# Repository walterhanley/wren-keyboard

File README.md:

# Wren Keyboard

## Table of Contents
- [Introduction](https://github.com/walterhanley/wren-keyboard#introduction)
- [Controller](https://github.com/walterhanley/wren-keyboard#controller)
- [PCB](https://github.com/walterhanley/wren-keyboard#pcb)
- [Case and Plate](https://github.com/walterhanley/wren-keyboard#case-and-plate)
- [Software](https://github.com/walterhanley/wren-keyboard#software)
- [Cost Estimates and Purchasing](https://github.com/walterhanley/wren-keyboard#cost-estimates-and-purchasing)
- [BOM](https://github.com/walterhanley/wren-keyboard#bom)
- [Build Guide](https://github.com/walterhanley/wren-keyboard#build-guide)

## Introduction
The Wren is a split ergonomic "system keyboard". It takes heavy inspiration from the Lily58, [Afternoon Labs' Breeze](https://afternoonlabs.com/breeze/), and [SplitKB's Kyria](https://blog.splitkb.com/blog/introducing-the-kyria), in addition to employing a case similar to the Corne's.

My primary keyboard for the last few years has been Prime Keyboards' prime_o, before which I used a handwired Planck. On both I made pretty heavy use of the numpad. I grew to appreciate the prime\_o's physical one, though, mostly because I spend a lot of time in Excel at my day job and like using the mouse and numpad simultaneously. I've been wanting to switch to ergo for a while, but I was annoyed by the thought of having to use a separate numpad to recreate that experience. This project was an attempt to solve that problem.

My original design simply incorporated a southpaw numpad. After some feedback, though, I decided to reinvent it as a "system keyboard" modeled after the old system cameras. The repository includes a universal PCB (incorporating break-away tabs) and plates to make four boards, each reversible:
- A Lilly58/Kyria-inspired split board, with no extra keys;
- An extended layout with a 4x4 numpad;
- An extended layout with a traditional nav cluster; and
- A small 4x4 macropad (nicknamed Egg).

Each of these boards (besides the macropad) can be combined with the others in a split setup, so users can take their pick of a right or left nav cluster/numpad, or combine both in the same board. You could even just use two of the basic boards together for a more traditional layout, though I'm sure there are more elegant designs out there for that.

## Controller
The Wren uses a Pro Micro-compatible footprint, but is designed around the Elite-C's extra I/O pins on the numpad board. With just a Pro Micro, the outer column won't work. I _think_ you could get a Nice!Nano to full compatibility with some creative soldering from the mid-board I/O pins to the appropriate pins on the Elite-C footprint, but I haven't spent any time on this myself.

## PCB
The PCB uses reversible, MX-compatible footprints. There isn't hot-swap support yet, in large part because I didn't want to deal with the structural considerations of those sockets. If someone else wanted to make a pull request for a hotswap version, though, I'd be happy to merge it in.

The PCB is also specifically designed around rotary encoders with a diameter less than 0.5". I'm using Kilo 50 sized knobs, but others in a similar size class will work well, too.

## Case and Plate
This repository includes a top and bottom plate designed around M2 screws and standoffs. The bottom plate can be manufactured out of FR4 PCB material by any manufacturer; this will likely be the most cost-effective option. The top plate cannot be manufactured by my preferred PCB fabricator, JLCPCB, but your milage may vary. Instead, I used the .eps files included in the [Case folder](https://github.com/walterhanley/wren-keyboard/tree/main/Case) to have my top plates manufactured in stainless steel by SendCutSend. In my experience these plates are an extremely tight fit around Kailh Box switches, but considering these aren't hot-swap that's an acceptable trade-off for me.

To make a complete case, you'll need 7 M2 spacers (5 for the plain board), a top plate, and a bottom plate.

Additionally, I've planned a 3D printed outer case. This design wraps the PCB and top plate in a printed outer layer, and provides a bit more protection.

## Software
Tested code for this board is waiting for approval in the [main QMK repository](https://github.com/qmk/qmk_firmware/pull/14570). If you'd like to download and work out of my fork, you can find it [here](https://github.com/walterhanley/qmk_firmware/tree/wren_initial). To build a hex file with the default keymap, use the following code after setting up your [QMK build environment](https://docs.qmk.fm/#/newbs_getting_started):

```
qmk compile -kb wren -km default
```

This can be flashed to your keyboard [in the usual way](https://docs.qmk.fm/#/newbs_flashing). The push-button below the microcontroler will put the keyboard into DFU mode. 

When customizing your keymap, note that the matrix includes all keys that would be present in a numpad-numpad pair. In other words, even if the left side of your physical keyboard lacks a numpad, your keymap.c file will include those keys. Feel free to either mark all those keys with a KC_NO keycode or leave them as-is--it's not like you can press them anyway :). As well, if you'd like to plug your USB cable into the right half instead of the default left, add the following to your config.h:

```
#define MASTER_RIGHT
```

If you end up implementing something for this board in ZMK please don't hesitate to let me know or submit a pull request--I'd be happy to include documentation of that here, as well.

## Cost Estimates and Purchasing
It should be relatively affordable to have these boards manufactured. Here are my costs for my PCB components at JLCPCB in USD as of September 2021:
- Universal PCB (15 boards): $35.30
- Numpad bottom plate (5 boards): $14.50
- Nav bottom plate (5 Boards): $13.60
- Plain bottom plate (5 boards): $10.80
- Egg bottom plate (5 boards): $2.00

And for my plates from SendCutSend:
- Numpad top plate (2 plates): $62.38
- Nav top plate: $34.94
- Plain top plate: $26.08

The repository should include up-to-date zipped Gerber files, which can be used to have PCBs fabbed at your manufacturer of choice. I'm partial to JLCPCB (which consistently has very low prices and now offers aluminum PCB options for plates), but OSHPark is a good option if you're in the US and like purple or want single boards. For best compatibility, please have both plates and cases manufactured with a 1.6mm or 1.5mm thickness.

(I'm currently not planning on offering these boards as a kit. It should be cost-competitive to source the cases and plates yourself, and getting comfortable with ordering PCBs is a great first step to designing your own custom board. If you are interested in stocking this keyboard, though, please feel free to reach out and I'll be happy to provide any help I can.)

## BOM
### Numpad Board
To assemble a numpad half, you'll need these parts:
- 1 Universal PCB
- 1 Numpad top plate
- 1 Numpad bottom plate
- 1 Elite-C microcontroller
- 7 8mm M2 threaded separators
- 14 4mm M2 screws
- 44 MX-style keyswitches
- 43 1u MX keycaps
- 1 2u MX keycaps
- 45 1N4148 diodes
- 1 Alps EC-11 compatible rotary encoder (Bourns PEC11L-4115F-S0020 recommended)
- 1 Rotary encoder knob (0.5" diameter or less)
- 1 2u PCB-mount cherry stabilizer
- 1 6mm push-button switch
- 1 PJ320E TRRS jack
- 2 4.7kΩ axial resistors

### Nav Cluster Board
To assemble a nav cluster half, you'll need these parts:
- 1 Universal PCB
- 1 Nav cluster top plate
- 1 Nav cluster bottom plate
- 1 Pro Micro compatible microcontroller
- 7 8mm M2 threaded separators
- 14 4mm M2 screws
- 38 MX-style keyswitches
- 37 1u MX keycaps
- 1 2u MX keycaps
- 39 1N4148 diodes
- 1 Alps EC-11 compatible rotary encoder (Bourns PEC11L-4115F-S0020 recommended)
- 1 Rotary encoder knob (0.5" diameter or less)
- 1 2u PCB-mount cherry stabilizer
- 1 6mm push-button switch
- 1 PJ320E TRRS jack
- 2 4.7kΩ axial resistors

### Plain Board
To assemble a nav cluster half, you'll need these parts:
- 1 Universal PCB
- 1 Plain top plate
- 1 Plain bottom plate
- 1 Pro Micro compatible microcontroller
- 7 8mm M2 threaded separators
- 14 4mm M2 screws
- 28 MX-style keyswitches
- 27 1u MX keycaps
- 1 2u MX keycap
- 29 1N4148 diodes
- 1 Alps EC-11 compatible rotary encoder (Bourns PEC11L-4115F-S0020 reccomended)
- 1 Rotary encoder knob (0.5" diameter or less)
- 1 2u PCB-mount cherry stabilizer
- 1 6mm push-button switch
- 1 PJ320E TRRS jack
- 2 4.7kΩ axial resistors

### Egg Macro Pad
To assemble an egg with a broken-off piece of a main board, you'll need these parts:
- 1 Universal PCB
- 1 Egg top plate
- 1 Egg bottom plate
- 1 Pro Micro compatible microcontroller
- 4 8mm M2 threaded separators
- 8 4mm M2 screws
- 12/16 MX-style keyswitches
- 12/16 1u MX keycaps
- 12/16 1N4148 diodes

## Build Guide
_Please note that this build guide refers to the "top" or "bottom" of the PCB. Since the PCB is reversible, these terms are relative to the final orientation of the board, not anything absolute. For example, the top of the right hand board would be the bottom of the left-hand board._

0. If necessary, break off any unused sections of the PCB. This is best accomplished by placing the board on a hard, flat surface with the perforated section of the board placed over the edge. While holding the main section of the board to the surface, firmly press down on the section you'd like to detach until it breaks off. Then, use a file to remove any remnants of the perforation. 

1. Next, place diodes on the bottom side of the PCB, taking care to place the diodes with the black stipe facing the square pad.

TIP: Use needle-nose pliers to assist in bending diodes, as shown below.

2. Solder the diodes in place on the bottom side of the board.

3. Place the resistors on the bottom side of the PCB and solder them into place.

4. Turn the board over and clip the leads of the resistors and diodes as close as possible to the PCB. To avoid fitment issues with switches, ensure that the leads are cut nearly flush; nail clippers are good for this purpose.

5. Place the headers for the microcontroller in place with the plastic spacer at the front of the board and secure them with a piece of painter's tape, taking care that they are perfectly straight. 

Using the tape to ensure the headers remain straight, tack solder a pin on each strip.

Remove any remaining tape and solder the remaining pins.

6. Solder the controller to the headers on the front of the board. The controller should be facing down on the left half, and up on the right half. 

7. Place the reset button below the controller on the front of the board and solder it into place.

8. Place the TRRS jack on the front of the PCB and solder it into place.

9. Place the rotary encoder on the front of the PCB and solder it into place. Take care to ensure the encoder is as straight as possible; it is possible for the encoder to interfere with the plate if it's attached incorrectly.

10. Place the stabilizer.

11. Snap the switches into the plate, taking care to match the orientation of the PCB. They will likely be a tight fit.

12. Fit the switchplate onto the PCB, taking care to fit it around the encoder as shown.

13. Tack solder the switchplate into place using the switches on the corners of the board.

14. Finish soldering the switchplate.

15. Attach the knob for the rotary encoder.

16. Attach the standoffs using a screw through the front of the PCB.

17. Clean off any excess flux using isopropyl alchohol.

18. Using the standoffs, attach the rear plate to the board.

19. Attach rubber bumpers to the rear of the board for stability.

20. Admire your work! Your board is ready to be flashed. If necessary, repeat with the other side of the board.

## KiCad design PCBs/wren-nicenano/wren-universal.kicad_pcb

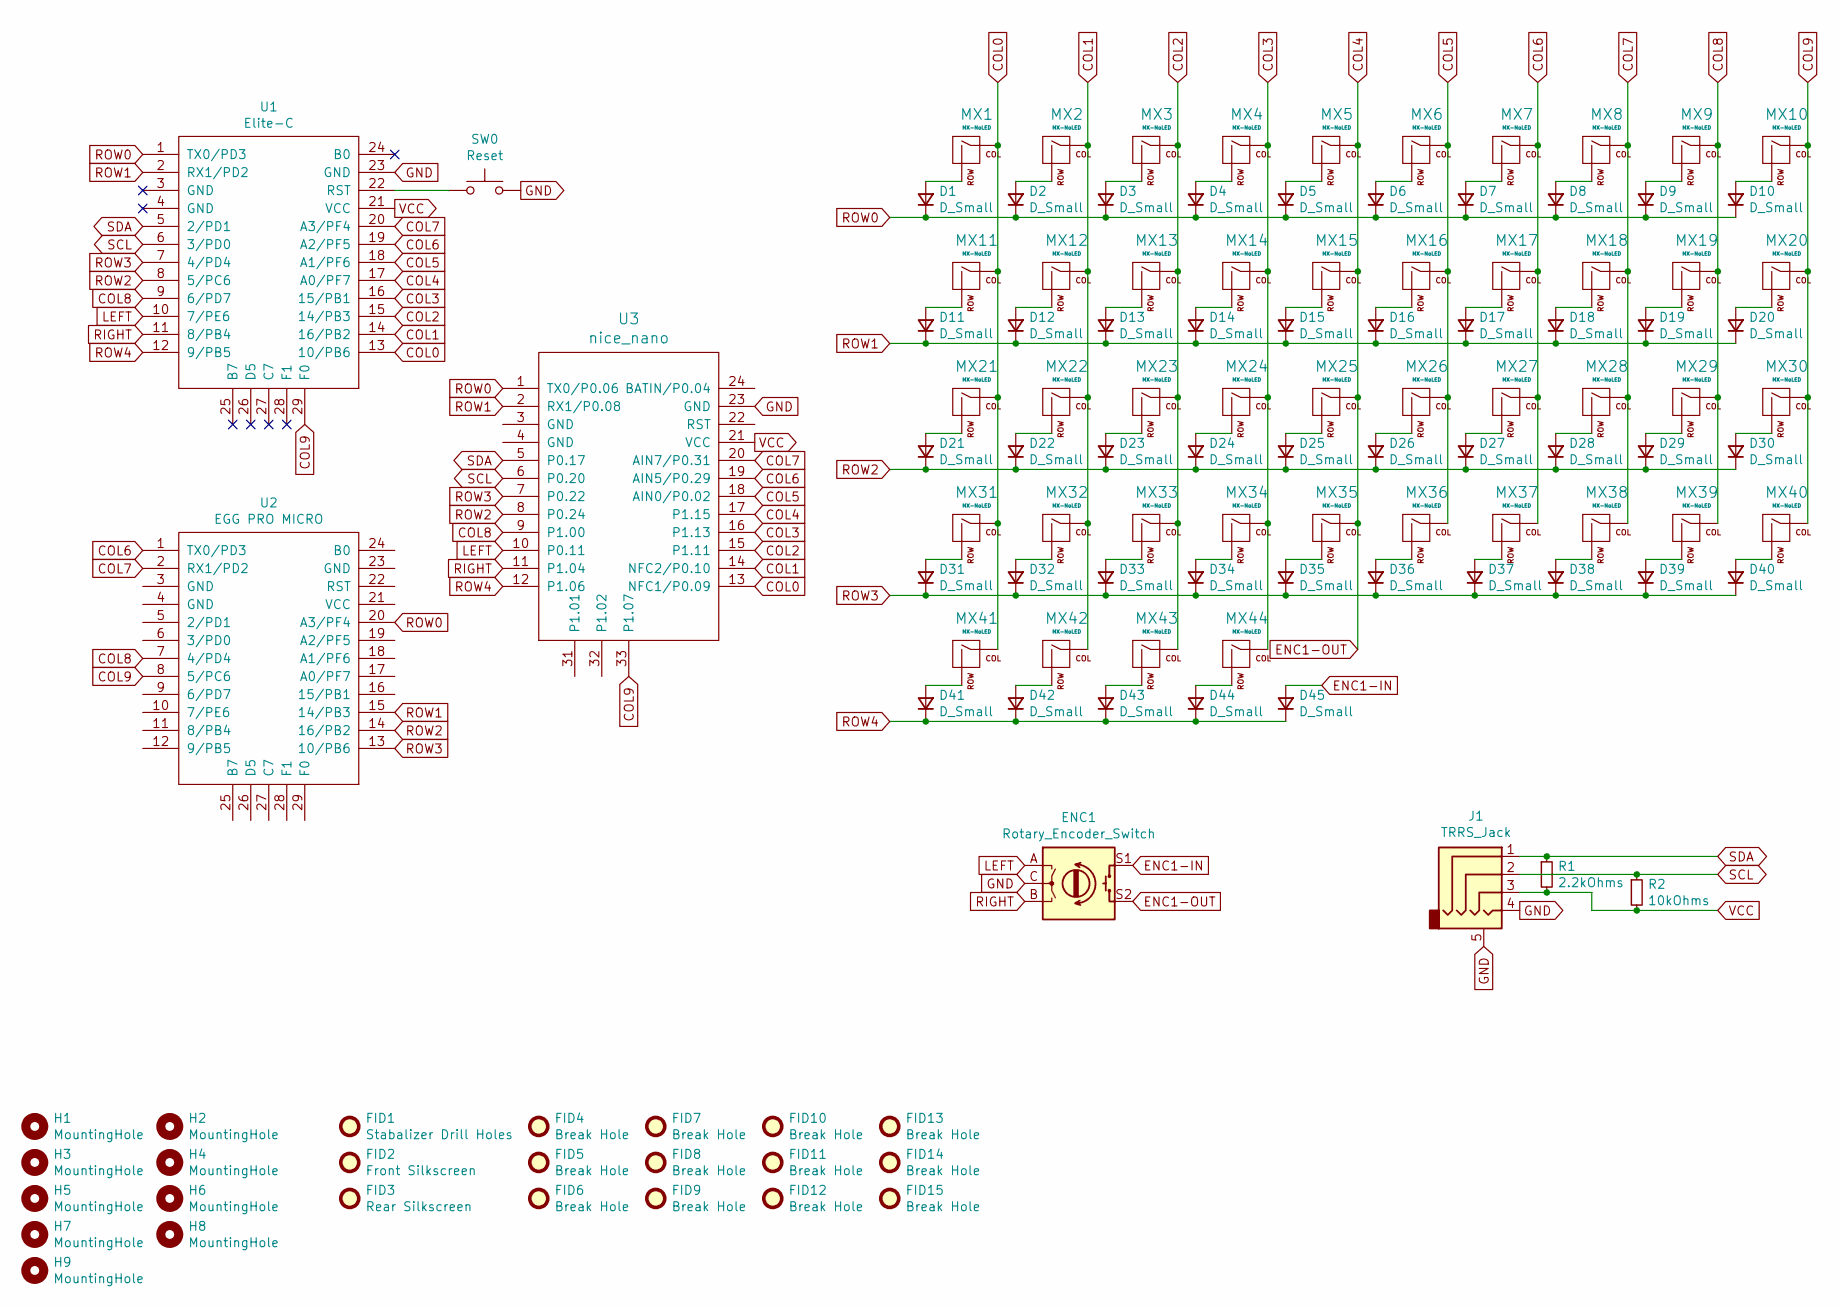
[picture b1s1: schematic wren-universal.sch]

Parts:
D1, D2, D3, D4, D5, D6, D7, D8, D9, D10, D11, D12, D13, D14, D15, D16, D17, D18, D19, D20, D21, D22, D23, D24, D25, D26, D27, D28, D29, D30, D31, D32, D33, D34, D35, D36, D37, D38, D39, D40, D41, D42, D43, D44, D45: D_Small; D_SOD123_axial
ENC1: Rotary_Encoder_Switch; RotaryEncoder_Alps_EC11E-Switch_Vertical_H20mm
FID1: Stabalizer Drill Holes; Stabilizer_MX_2u
FID2: Front Silkscreen; wren_logo
FID3: Rear Silkscreen; wren_logo
FID4, FID5, FID6, FID7, FID8, FID9, FID10, FID11, FID12, FID13, FID14, FID15: Break Hole; MountingHole_2.1mm
H1, H2, H3, H4, H5, H6, H7, H8, H9: MountingHole; MountingHole_5.5mm
J1: TRRS_Jack; TRRS_JACK_MJ4PP9
MX1, MX2, MX3, MX4, MX5, MX6, MX7, MX8, MX9, MX10, MX11, MX12, MX13, MX14, MX15, MX16, MX17, MX18, MX19, MX20, MX21, MX22, MX23, MX24, MX25, MX26, MX27, MX28, MX29, MX30, MX31, MX32, MX33, MX34, MX35, MX36, MX37, MX38, MX39, MX40, MX41, MX42, MX43, MX44: MX-NoLED; SW_MX_reversible
R1: 2.2kOhms; R_Axial_DIN0204_L3.6mm_D1.6mm_P5.08mm_Vertical
R2: 10kOhms; R_Axial_DIN0204_L3.6mm_D1.6mm_P5.08mm_Vertical
SW0: Reset; SW_PUSH_6mm
U1: Elite-C
U2: EGG PRO MICRO; ARDUINO_PRO_MICRO
U3: nice_nano

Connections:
COL0: MX1.1 (COL), MX11.1 (COL), MX21.1 (COL), MX31.1 (COL), MX41.1 (COL), U1.13 (10/PB6), U3.13 (NFC1/P0.09)
COL1: MX2.1 (COL), MX12.1 (COL), MX22.1 (COL), MX32.1 (COL), MX42.1 (COL), U1.14 (16/PB2), U3.14 (NFC2/P0.10)
COL2: MX3.1 (COL), MX13.1 (COL), MX23.1 (COL), MX33.1 (COL), MX43.1 (COL), U1.15 (14/PB3), U3.15 (P1.11)
COL3: MX4.1 (COL), MX14.1 (COL), MX24.1 (COL), MX34.1 (COL), MX44.1 (COL), U1.16 (15/PB1), U3.16 (P1.13)
COL4: ENC1.S2, MX5.1 (COL), MX15.1 (COL), MX25.1 (COL), MX35.1 (COL), U1.17 (A0/PF7), U3.17 (P1.15)
COL5: MX6.1 (COL), MX16.1 (COL), MX26.1 (COL), MX36.1 (COL), U1.18 (A1/PF6), U3.18 (AIN0/P0.02)
COL6: MX7.1 (COL), MX17.1 (COL), MX27.1 (COL), MX37.1 (COL), U1.19 (A2/PF5), U2.1 (TX0/PD3), U3.19 (AIN5/P0.29)
COL7: MX8.1 (COL), MX18.1 (COL), MX28.1 (COL), MX38.1 (COL), U1.20 (A3/PF4), U2.2 (RX1/PD2), U3.20 (AIN7/P0.31)
COL8: MX9.1 (COL), MX19.1 (COL), MX29.1 (COL), MX39.1 (COL), U1.9 (6/PD7), U2.7 (4/PD4), U3.9 (P1.00)
COL9: MX10.1 (COL), MX20.1 (COL), MX30.1 (COL), MX40.1 (COL), U1.29 (F0), U2.8 (5/PC6), U3.33 (P1.07)
ENC1-IN: D45.2 (A), ENC1.S1
GND: ENC1.C, J1.4, J1.5, SW0.2, U1.23 (GND), U3.23 (GND)
LEFT: ENC1.A, U1.10 (7/PE6), U3.10 (P0.11)
unnamed: D1.2 (A), MX1.2 (ROW)
unnamed: D2.2 (A), MX2.2 (ROW)
unnamed: D3.2 (A), MX3.2 (ROW)
unnamed: D4.2 (A), MX4.2 (ROW)
unnamed: D5.2 (A), MX5.2 (ROW)
unnamed: D6.2 (A), MX6.2 (ROW)
unnamed: D7.2 (A), MX7.2 (ROW)
unnamed: D8.2 (A), MX8.2 (ROW)
unnamed: D9.2 (A), MX9.2 (ROW)
unnamed: D10.2 (A), MX10.2 (ROW)
unnamed: D11.2 (A), MX11.2 (ROW)
unnamed: D12.2 (A), MX12.2 (ROW)
unnamed: D13.2 (A), MX13.2 (ROW)
unnamed: D14.2 (A), MX14.2 (ROW)
unnamed: D15.2 (A), MX15.2 (ROW)
unnamed: D16.2 (A), MX16.2 (ROW)
unnamed: D17.2 (A), MX17.2 (ROW)
unnamed: D18.2 (A), MX18.2 (ROW)
unnamed: D19.2 (A), MX19.2 (ROW)
unnamed: D20.2 (A), MX20.2 (ROW)
unnamed: D21.2 (A), MX21.2 (ROW)
unnamed: D22.2 (A), MX22.2 (ROW)
unnamed: D23.2 (A), MX23.2 (ROW)
unnamed: D24.2 (A), MX24.2 (ROW)
unnamed: D25.2 (A), MX25.2 (ROW)
unnamed: D26.2 (A), MX26.2 (ROW)
unnamed: D27.2 (A), MX27.2 (ROW)
unnamed: D28.2 (A), MX28.2 (ROW)
unnamed: D29.2 (A), MX29.2 (ROW)
unnamed: D30.2 (A), MX30.2 (ROW)
unnamed: D31.2 (A), MX31.2 (ROW)
unnamed: D32.2 (A), MX32.2 (ROW)
unnamed: D33.2 (A), MX33.2 (ROW)
unnamed: D34.2 (A), MX34.2 (ROW)
unnamed: D35.2 (A), MX35.2 (ROW)
unnamed: D36.2 (A), MX36.2 (ROW)
unnamed: D37.2 (A), MX37.2 (ROW)
unnamed: D38.2 (A), MX38.2 (ROW)
unnamed: D39.2 (A), MX39.2 (ROW)
unnamed: D40.2 (A), MX40.2 (ROW)
unnamed: D41.2 (A), MX41.2 (ROW)
unnamed: D42.2 (A), MX42.2 (ROW)
unnamed: D43.2 (A), MX43.2 (ROW)
unnamed: D44.2 (A), MX44.2 (ROW)
unnamed: SW0.1, U1.22 (RST)
RIGHT: ENC1.B, U1.11 (8/PB4), U3.11 (P1.04)
ROW0: D1.1 (K), D2.1 (K), D3.1 (K), D4.1 (K), D5.1 (K), D6.1 (K), D7.1 (K), D8.1 (K), D9.1 (K), D10.1 (K), U1.1 (TX0/PD3), U2.20 (A3/PF4), U3.1 (TX0/P0.06)
ROW1: D11.1 (K), D12.1 (K), D13.1 (K), D14.1 (K), D15.1 (K), D16.1 (K), D17.1 (K), D18.1 (K), D19.1 (K), D20.1 (K), U1.2 (RX1/PD2), U2.15 (14/PB3), U3.2 (RX1/P0.08)
ROW2: D21.1 (K), D22.1 (K), D23.1 (K), D24.1 (K), D25.1 (K), D26.1 (K), D27.1 (K), D28.1 (K), D29.1 (K), D30.1 (K), U1.8 (5/PC6), U2.14 (16/PB2), U3.8 (P0.24)
ROW3: D31.1 (K), D32.1 (K), D33.1 (K), D34.1 (K), D35.1 (K), D36.1 (K), D37.1 (K), D38.1 (K), D39.1 (K), D40.1 (K), U1.7 (4/PD4), U2.13 (10/PB6), U3.7 (P0.22)
ROW4: D41.1 (K), D42.1 (K), D43.1 (K), D44.1 (K), D45.1 (K), U1.12 (9/PB5), U3.12 (P1.06)
SCL: J1.2, R2.1, U1.6 (3/PD0), U3.6 (P0.20)
SDA: J1.1, R1.1, U1.5 (2/PD1), U3.5 (P0.17)
VCC: J1.3, R1.2, R2.2, U1.21 (VCC), U3.21 (VCC)

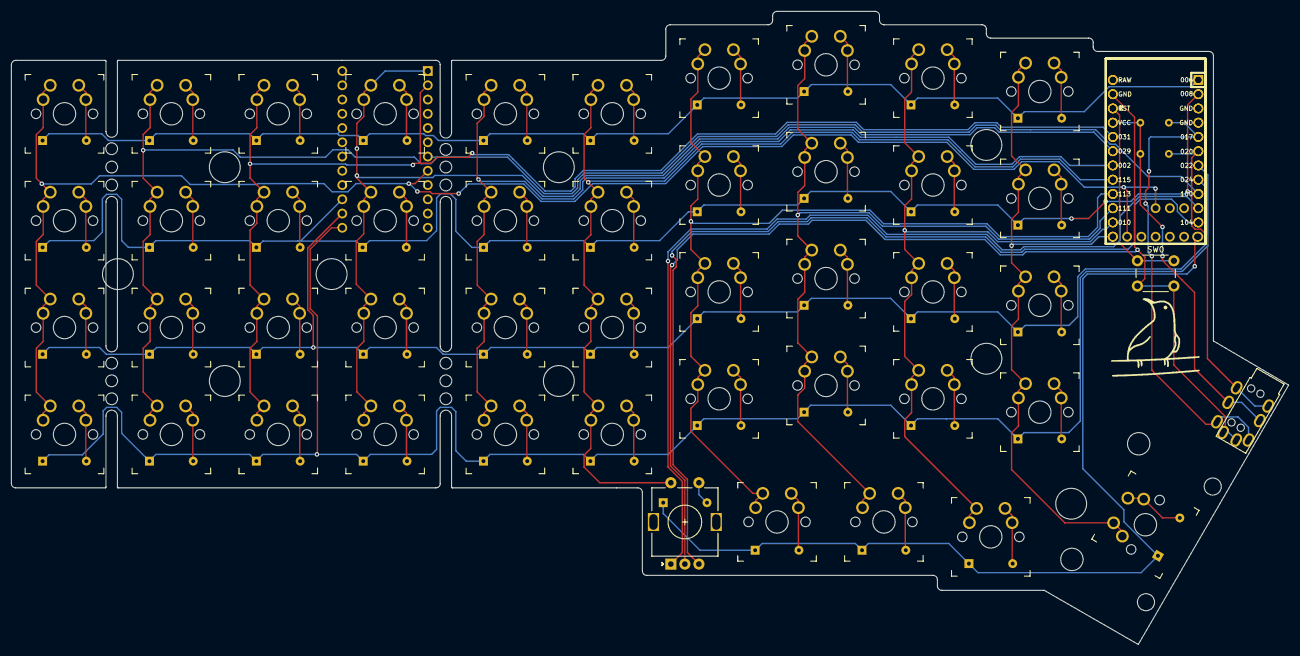
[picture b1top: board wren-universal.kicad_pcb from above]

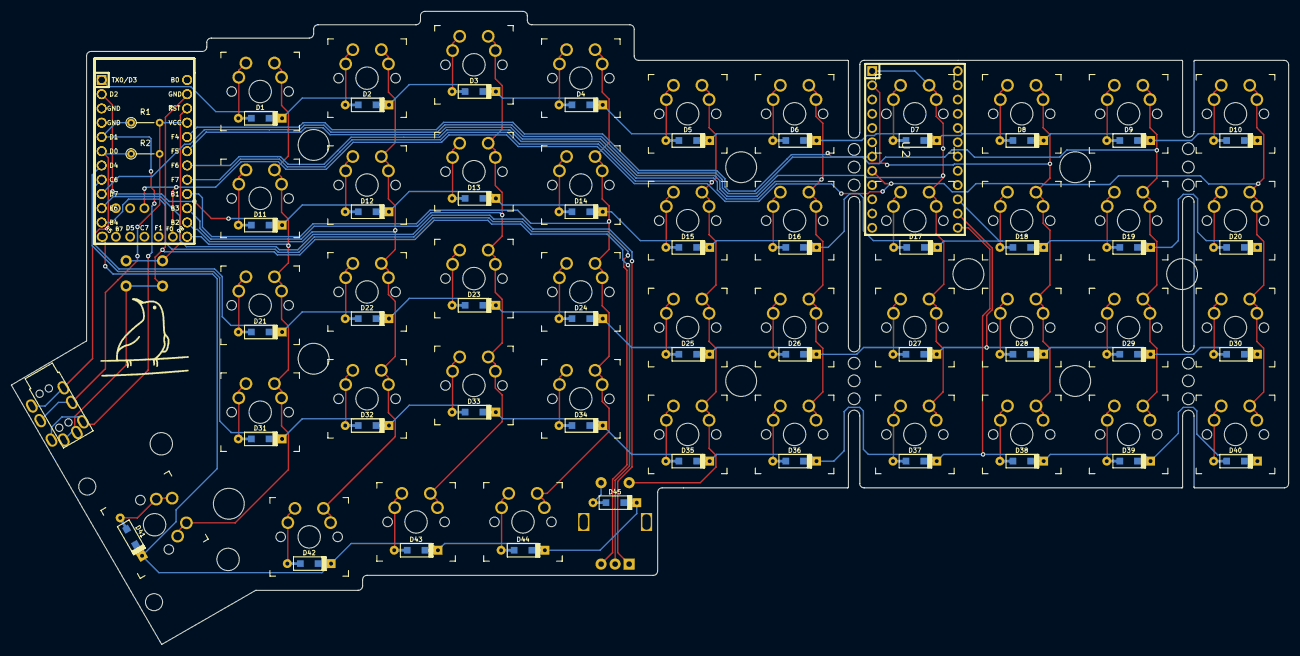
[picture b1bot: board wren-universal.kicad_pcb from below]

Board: 2 copper layers, 227.7 x 112.8 mm, 121 parts (51 on the bottom side), 67 nets.

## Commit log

2021-04-27 Update screw positions on plates to match universal PCBs, update Gerbers
2021-04-27 Add Universal PCB Image
2021-04-27 Add Egg detachable macro pad
2021-04-27 Update readme for Egg
    Update readme to add references to the Egg macropad, as well as add Egg plate Gerbers
2021-05-08 Minor Changes
2021-05-09 Clean up design rules, traces.
2021-07-09 Prototype (absurdly expensive) LEMO interconnect
    Mostly just playing around with this. If you wanted to do it seriously the connectors would cost more than the keyboard.
2021-09-05 Finalized 1.0 Gerbers
2021-09-11 Create .svg for top plates
    On realizing that my PCB plates weren't really manufacturable, I decided to use those KiCad files to make a .svg of my plate design that could be laser cut by services like SendCutSend.
2021-09-22 Add Table of Contents
2021-09-26 Add Tutorial to Readme, along with pictures
2021-09-26 Add more detail on rubber bumpers
2021-09-26 Update image reference
2021-09-26 Add glamor shot
2021-10-08 Update README.md to add references to my QMK fork
    This adds documentation of my QMK fork, as well as the pull request for the board in the main QMK repository. This is very much a placeholder until the code is merged, but considering that might take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
2021-10-25 Add initial pass at footprint
2022-02-28 Add credit for noroadsleft to readme.md
